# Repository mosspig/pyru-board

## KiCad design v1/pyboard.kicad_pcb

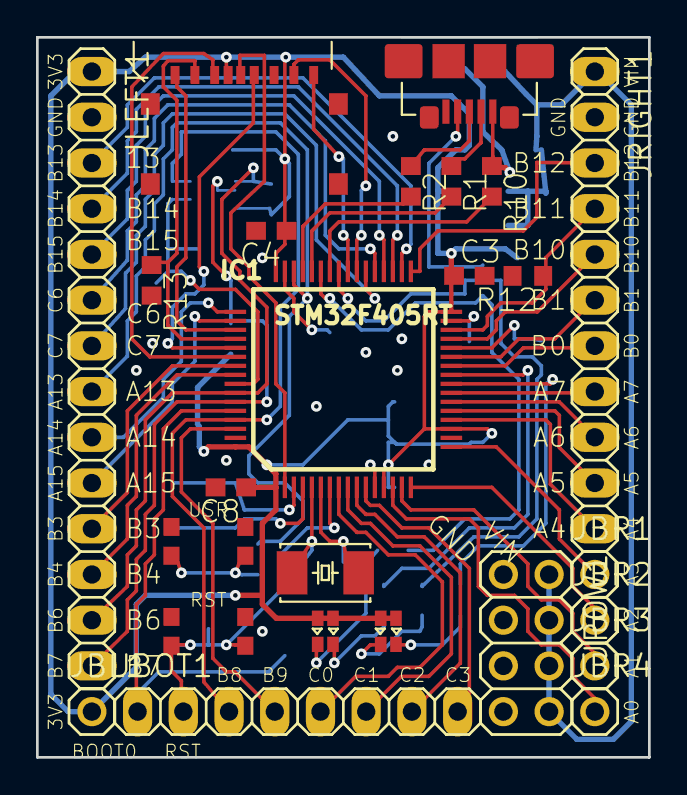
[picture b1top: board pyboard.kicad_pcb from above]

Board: 2 copper layers, 34.0 x 40.0 mm, 58 parts (0 on the bottom side), 67 nets.

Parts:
C1, C2, C11, C12: 12p; C0603
C3, C4, C5, C6, C8, C9, C13, C14, C15: 100n; C0603
C7: 4u7; C0603
C10, C16, C17: 1u; C0603
C11B1, C12B1: 2u2; C0603
D1: 1N5819; SOD-123
IC1: STM32F405RT; LQFP64
JBL1: 1; 1X01
JBOT1: 8; 1X08
JBR1, JBR2, JBR3, JBR4: 1; 1X01
JLEFT1: 14; 1X14
JPOW1: 8; 2X04
JRIGHT1: 11; 1X11
Q1: 8MHz; TXC-SMD-50X32
Q2: 32.768kHz; TXC-SMD-32X15
R1, R2: 22; R0603
R3, R17: 10k; R0603
R4, R5, R6, R7: 560; R0603
R8, R9: 4k7; R0603
R10, R11: 1k; R0603
R12, R14, R15: 100k; R0603
R13: 10M; R0603
R16: 0; R0603
R18: 0; R0805
U1: MCP1802; SOT-23-5
U$1, U$6: LTST-C195KGJRKT; LTST-BILED-15X16
U$2, U$3: KMR4TACTILE; KMR4SWITCH
U$4: MOLEX-SD-105027; MOLEX-SD-105027-PKG
U$5: MMA7660; DFN10
U$7: USB-MICRO-AB; HRS-USB-ZX62D-AB-5P8-PKG

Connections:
+3V3: C3.1, C4.1, C5.1, C6.1, C7.1, C8.1, C9.1, C10.1, C14.1, C17.1, IC1.1, IC1.13, IC1.19, IC1.32, IC1.48, IC1.64, JBL1.1, JLEFT1.1, R3.1, R8.1, R9.1, U1.P$5, U$1.P$1, U$1.P$2, U$4.P$4, U$5.P$9, U$6.P$1, U$6.P$2
/BOOT0: IC1.60, JBOT1.1, R15.1
/FS_DM: IC1.44, R1.2
/FS_DP: IC1.45, R2.2
/FS_VUSB: IC1.42, R10.2
/IO_PA0: IC1.14, JBR4.1
/IO_PA1: IC1.15, JBR3.1
/IO_PA2: IC1.16, JBR2.1
/IO_PA3: IC1.17, JBR1.1
/IO_PA4: IC1.20, JRIGHT1.11
/IO_PA5: IC1.21, JRIGHT1.10
/IO_PA6: IC1.22, JRIGHT1.9
/IO_PA7: IC1.23, JRIGHT1.8
/IO_PA14: IC1.49, JLEFT1.9
/IO_PA15: IC1.50, JLEFT1.10
/IO_PB0: IC1.26, JRIGHT1.7
/IO_PB1: IC1.27, JRIGHT1.6
/IO_PB2: IC1.28, R11.1
/IO_PB3: IC1.55, JLEFT1.11
/IO_PB4: IC1.56, JLEFT1.12
/IO_PB9: IC1.62, JBOT1.4
/IO_PB10: IC1.29, JRIGHT1.5
/IO_PB11: IC1.30, JRIGHT1.4, R12.1
/IO_PB12: IC1.33, JRIGHT1.3
/IO_PB13: IC1.34, JLEFT1.3
/IO_PB14: IC1.35, JLEFT1.4
/IO_PB15: IC1.36, JLEFT1.5
/IO_PC0: IC1.8, JBOT1.5
/IO_PC1: IC1.9, JBOT1.6
/IO_PC2: IC1.10, JBOT1.7
/IO_PC3: IC1.11, JBOT1.8
/IO_PC6: IC1.37, JLEFT1.6
/IO_PC7: IC1.38, JLEFT1.7
/LEDG1: IC1.24, R4.1
/LEDG2: IC1.25, R7.1
/LEDR1: IC1.41, R6.1
/LEDR2: IC1.43, R5.1, R16.2
/MMA_AVDD: C15.1, IC1.57, R14.1, U$5.P$3
/MMA_INT: IC1.61, JBOT1.3, U$5.P$5
/MMA_SCL: IC1.58, JLEFT1.13, R9.2, U$5.P$6
/MMA_SDA: IC1.59, JLEFT1.14, R8.2, U$5.P$7
/NRST: C13.1, IC1.7, JBOT1.2, R3.2, U$2.P$3, U$2.P$4
/SDIO_CK: IC1.53, U$4.P$5
/SDIO_CMD: IC1.54, U$4.P$3
/SDIO_D0: IC1.39, U$4.P$7
/SDIO_D1: IC1.40, U$4.P$8
/SDIO_D2: IC1.51, U$4.P$1
/SDIO_D3: IC1.52, R13.1, U$4.P$2
/SDIO_SW: IC1.2, U$4.G$1
/USR_SW: IC1.46, JLEFT1.8, R17.1
/VIN: C16.1, D1.K, JPOW1.2, JPOW1.4, JPOW1.6, JPOW1.8, JRIGHT1.1, R18.1, U1.P$1, U1.P$3
/VUSB: D1.A, R10.1, R18.2, U$7.P$1
GND: C1.1, C2.1, C3.2, C4.2, C5.2, C6.2, C7.2, C8.2, C9.2, C10.2, C11.1, C11B1.2, C12.1, C12B1.2, C13.2, C14.2, C15.2, C16.2, C17.2, IC1.12, IC1.18, IC1.63, JLEFT1.2, JPOW1.1, JPOW1.3, JPOW1.5, JPOW1.7, JRIGHT1.2, R11.2, R12.2, R13.2, R14.2, R15.2, U1.P$2, U$2.P$1, U$2.P$2, U$3.P$1, U$3.P$2, U$4.P$6, U$5.P$1, U$5.P$2, U$5.P$4, U$5.P$8, U$5.P$10, U$7.P$5
unnamed: C1.2, IC1.6, Q1.P$2
unnamed: C2.2, IC1.5, Q1.P$1
unnamed: C11.2, IC1.4, Q2.P$2
unnamed: C11B1.1, IC1.47
unnamed: C12.2, IC1.3, Q2.P$1
unnamed: C12B1.1, IC1.31
unnamed: R1.1, U$7.P$2
unnamed: R2.1, U$7.P$3
unnamed: R4.2, U$1.P$3
unnamed: R5.2, U$6.P$4
unnamed: R6.2, U$1.P$4
unnamed: R7.2, U$6.P$3
unnamed: R16.1, U$7.P$4
unnamed: R17.2, U$3.P$3, U$3.P$4
